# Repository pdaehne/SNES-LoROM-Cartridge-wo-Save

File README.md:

# Super Nintendo LoROM Cartridge without Save

This repository contains the KiCad project and Gerber files for a Super Nintendo
LoROM Cartridge without Save functionality that allows to create replica
cartridges using 27C400, 27C800 and 27C160 EPROMS. When you have SNES
cartridge images (usually SFC files), you can burn one or more of them onto the
EPROM (depending on the size), and use the cartridge on your SNES like a normal
cartridge.

What is a LoROM cartridge, and how do you know that a given cartridge image
needs a LoROM cartridge PCB? Well, there are three types of SNES cartridges,
LoROM, HiROM and ExHiROM. Most cartridge images have a header that specifies
the type of cartridge (a notable exception are the test cartridges, which are
both LoROM cartridges, but do not have a header). There are software tools out
there that allow you to view the information in the cartridge image, and you
can use such a tool to determine whether a given image needs a LoROM, HiROM or
ExHiROM cartridge PCB.

## Ordering the PCB

The subdirectory "gerber-files" contains a Zip file you can use to order the PCB
from PCB manufacturers like PCBWay or JLCPCB. Simply upload the Zip on their web
page.

> [!IMPORTANT]
> SNES cartridges have a thickness of 1.2mm, not the default thickness of 1.6mm!
> Make sure that you order your PCBs with a thickness of 1.2mm. I also recommend
> to order a surface finish of ENIG with gold fingers and chamfered edges,
> because it is much more durable than the default HASL finish.

## Building the Cartridge

### Bill of Materials

* __1x 27C400, 27C800 or 27C160 EPROM__.

  This is where you store your cartridge images. 27C400 have a capacity of
  512 KiB, 27C800 a capacity of 1 MiB, and 27C160 a capacity of 2 MiB.

* (Optional) __1x 42 Pin Socket 2.54mm pitch 15.42mm width__.

  This is the socket for the EPROM. It is optional, you can also solder the
  EPROM directly to the PCB, but I prefer to use sockets. Keep in mind that the
  cartridge will not fit into a cartridge shell when you use sockets.

* __1x PIC12F629-I/P DIP-8__.

  This microcontroller simulates the CIC chip that is required on SNES
  cartridges. When powering on the console, the SNES communicates with this
  chip and starts the cartridge only when it is convinced that there is a
  legit CIC chip on the cartridge. This was a security scheme enforced by
  Nintendo to make sure that only properly licensed cartridges worked on the
  SNES. Today, this scheme is cracked, and we use this PIC instead of a real
  CIC.

* (Optional) __1x 8 Pin Socket 2.54mm pitch 7.62mm width__.

  This is the socket for the PIC12F629. It is optional, you can also solder the
  PIC directly to the PCB.

* __2x 100nF Ceramic Capacitors__.

  These are the decoupling capacitors for the EPROM and the PIC.

* __1x 22&mu;F Electrolytic Capacitor__.

  Another capacitor that improves the power supply for the ICs on the cartridge.

* (Optional) __3x 10kOhm Resistors__.

  Three pull-up resistors, one for the "/PAIR" input of the PIC (required), and
  two for the address lines A18 and A19 which get switched by the DIP switch
  (optional, only required when you actually install the DIP switch).

* (Optional) __1x DIP Switch 2 Pin__.

  This DIP switch is optional, it allows you to put multiple (up to four) images
  onto the cartridge and select one of them by switching the address lines A18
  and A19 of the EPROM. When you plan to put only one image onto the cartridge,
  you do not need this DIP switch and its two corresponding pull-up resistors,
  instead close two corresponding jumpers on the other side of the PCB.

### Soldering the Socket for the EPROM (U1)

Start with soldering the large 42 pin socket for the EPROM (U1). This socket is
optional, you can also solder the EPROM directly to the PCB, but I prefer to use
sockets. Keep in mind that the cartridge will not fit into a cartridge shell
when you use sockets.

When you solder the EPROM directly to the PCB, you have program it before doing
so! See below for more information.

Make sure the little notch of the socket is aligned with the little notch on the
silk screen (to the right in the image below).

### Soldering the Socket for the PIC12F629 (U2)

Now solder the small 8 pin socket for the PIC12F629 (U2). This socket is also
optional, you can also solder the PIC directly to the PCB.

When you solder the PIC directly to the PCB, you have program it before doing
so! See below for more information.

Make sure the little notch of the socket is aligned with the little notch on the
silk screen (to the right in the image below).

### Soldering the Decoupling Capacitors C1 and C2

Solder the two decoupling capacitors C1 and C2 for the EPROM and the PIC.

### Soldering the Pullup Resistors R1, R2 and R3

Solder the three pullup resistors R1, R2 and R3. R1 and R2 are the pullup
resistors for the address lines A18 and A19. They are optional, you only need to
install them when you install the DIP switch (see next step for more
information). R3 is the pullup resistor for the "/PAIR" input of the PIC and is
required.

### Soldering the DIP Switch

The DIP switch is optional, it is only required when you plan to put more than
one cartridge image onto the EPROM. When you install it, you also have to
install the pullup resistors R1 and R2. When you do not install it, you have to
close the corresponding jumpers on the other side of the PCB with a blob of
solder.

### Soldering the Capacitor C3

The last step is to solder the electrolytic capacitor C3. I recommend to bend
the legs of the capacitor so that it lies flat on the PCB. Keep in mind that the
orientation of this capacitors matters. The silk screen shows a small + on the
positive side of the footprint (left in the photo below), and a thick white
stripe on the negative side (right in the photo). The capacitor also has a white
stripe on its enclosure that marks the negative side. Another hint is the length
of the legs - the long leg is the positive side, and the short leg is the
negative side.

## Programming the Firmware on the PIC12F629

On each cartridge there has to be a CIC chip that proves to the console that
this is a legit cartridge licensed by Nintendo. Nowadays, this security chip is
cracked, and we can simulate it with a cheap PIC microprocessor and a special
firmware. The firmware is called "supercic", and precompiled versions
(.hex-Files) are available for download here:

https://sd2snes.de/blog/cool-stuff/supercic

The actual source code (if you are interested) is available on Github:

https://github.com/mrehkopf/sd2snes/tree/master/cic/supercic

What you need for programming the PIC is the file "supercic-key_p12f629.hex"
inside the zip file from the first link and of course a programmer. I own the
popular TL866 II Plus and will demonstrate how to install the firmware using
this programmer and the corresponding Xgpro software, but the approach will be
similar when using other types of programmers.

First, insert the PIC12F629 into the programmer like shown in the picture above.
The notch faces the lever (right in the image).

Then, start the Xgpro software, select the PIC12F629 IC, load
"supercic-key_p12f629.hex", and program the PIC. It is important to realize that
the .hex-File contains three parts, the Flash (code) section with the firmware,
the EEPROM (persistent memory) section with the PAL/NTSC flag, and the Fuses.
The Xgpro software will programm all three sections in one go, but when you use
another programmer and software combination, you might have to program these
three parts separately. Either way, carefully check that all parts got
programmed correctly, otherwise the cartridge will not work.

## Programming Cartridge Images on the EPROM

Now, we will programm the EPROM with the cartridge images. First of all, you
have to think about the layout of your cartridge images on the EPROM. This
depends on the size of your images and the size of your EPROM.

When you use a 27C400 EPROM, you have one single slot of 512 KiB where you can
program one single image with up to 512 KiB.

When you use a 27C800 EPROM, you have two slots of 512 KiB each. You can fill
these slots with two images of up to 512 KiB, one image in slot 1, and another
image in slot 2. Or you can fill these slots with one single image of up to 1
MiB that occupies both slots 1 and 2.

When you use a 27C160 EPROM, you have four slots of 512 KiB each. You can fill
these slots with four images up to 512 KiB, one image in each of the four slots.
Or you can fill these slots with two images of up to 1 MiB, one in slots 1 and
2, and the other in slots 3 and 4. You can also mix two images of 512 KiB with
one image of 1 MiB, with the two 512 KiB images in slots 1 and 2, and the 1 MiB
image in slots 2 and 3, or the other way round (the 1 MiB image in slots 1 and
2, and the two 512 KiB images in slots 3 and 4). Keep in mind that the start of
the 1 MiB image must be aligned to 1 MiB, i.e. putting a 1 MiB image into slots
2 and 3 is not possible! Finally, you can fill the slots with one single image
of up to 2 MiB that occupies slots 1, 2, 3 and 4.

As an example, I will programm a 27C160 EPROM (4 slots) for a test cartridge.
This cartridge will consist of the the following three cartridge images:

1. The "NTF 2.5 Test Cartridge", available here:

   https://tcrf.net/NTF_2.5_Test_Cartridge

   This is a 1 MiB image and will occupy slots 1 and 2.

2. The "Burn-in / Test Cartridge", available here:

   https://tcrf.net/Burn-in_-_Test_Cartridge

   This is a 512 KiB image and will occupy slot 3.

3. The "240p Test Suite", available here:

   https://artemiourbina.itch.io/240p-test-suite

   This is a 512 KiB image and will occupy slot 4.

My TL866 programmer is not able to programm the kinds of EPROMs needed for the
cartridge, but there are adapters available. I'm using the adapter from this
project:

https://github.com/mafe72/27c160-tl866-adapter

There are other alternatives available, for example this project:

https://github.com/keirf/pcb-projects/wiki/EPROM-Adapter-v4

Put the adapter into the TL866, and put the EPROM into the adapter as shown in
the image above.

These adapters are not able to programm the 27C160 in one single pass, instead
you have to write chunks of 512 KiB, which coincides nicely with our slots of
512 KiB. You have to set switches on the adapter to program the chunks into the
right location on the EPROM, but this depends on the adapter you are using. Have
a look into the manual for your adapter. The whole procedure is quite tedious,
and you have to be fully concentrated not to make an error. The slightest error,
and you have to clear your EPROM in your UV eraser and start over from the
beginning!

In the Xgpro software, select the "AT27C4096 @DIP40" IC. Yes, this is not the
EPROM we are using, but this is the way these adapters work. The 27C4096 is a
512 KiB EPROM that uses the same programming algorithm than our 27C160, and we
use it to program our 27C160 with chunks of 512 KiB. We have to deselect "Check
ID" for obvious reasons as well as "Pin Detect", and we have to set "Puls Delay"
to "50us". Finally, we have to adjust "VPP Voltage", have a look into the
datasheet for your EPROM. The datasheet for my ST M27C160 says that the
programming voltage has be "12.00V".

Now load the cartridge image for the first slot, in our case the "NTF 2.5 Test
Cartridge". This image is 1 MiB, i.e. it is too large, but this is not a
problem, Xgpro will automatically remove the surplus 512 KiB. Configure your
adapter for writing the first slot, and program the image.

Now we have to program the second half of the "NTF 2.5 Test Cartridge" into the
second slot. Again load the cartridge image, but in the file load dialog, set
the "From File Start Addr(Hex)" to "40000" (this is 512 KiB in [hexadecimal
notation](https://en.wikipedia.org/wiki/Hexadecimal)). Leave all the other
settings as for the first slot, configure your adapter for the second slot, and
program the second half of the image.

Now we have to program the "Burn-in / Test Cartridge" into the third slot. Load
the image, and make sure that in the file load dialog the "From File Start
Addr(Hex)" is set back to "00000". Leave all the other settings as for the first
two slots, configure your adapter for the third slot, and program the image.

Finally, we have to program the "240p Test Suite" into the fourth slot. You know
the drill. Load the image, leave all the other settings as before, configure
your adapter for the fourth slot, and program the image. Finished!

## Using the Cartridge and Troubleshooting

When you do not install your cartridge into a cartridge shell, you have to be
extremly careful when inserting the cartridge. Especially, you have to mind the
orientation: It is a little bit counter intuitive, but you have to insert the
cartridge backwards, with the components on the cartridge facing the back side
of the console! Also keep in mind that the cartridge slot in the console is much
wider than the edge connector of the cartridge because it has extension pins on
both sides that the cartridge does not use, so make sure to insert your
cartridge properly into the center section of the cartridge slot. And when you
remove the cartridge, do not use the eject button, and be careful that the
cartridge does not get stuck in the cover that protects the cartridge slot!

When you have more than one cartridge image programmed on your EPROM, you can
use the dip switches on the cartridge to select the image to start. To start
a given image on the EPROM, you have the select the slot where the image starts
with the two DIP switches:

* To select the image that starts at slot 1, switch both A18 and A19 to "on".

* To select the image that starts at slot 2, switch A18 to "off" and and A19 to
  "on".

* To select the image that starts at slot 3, switch A18 to "on" and and A19 to
  "off".

* To select the image that starts at slot 4, switch both A18 and A19 to "off".

| Slot 1                           | Slot 2                           | Slot3                            | Slot4                            |
|----------------------------------|----------------------------------|----------------------------------|----------------------------------|
|||||

As an example, lets have a look at the example cartridge we programmed in the
previous section. First, we want to start the "NTF 2.5 Test Cartridge". This
image starts in slot 1. So we have to move both DIP switches for A18 and A19 to
the "on" position.

Now we want to start the "Burn-in / Test Cartridge". This image starts in slot
3. So we have to move the DIP switch for address line A18 to "on", and the
DIP switch for address line A19 to "off".

Finally we want to start the "240p Test Suite". This image starts in slot 4. So
we have to move both DIP switches for A18 and A19 to the "off" position.

What happens when we select slot 2 on this cartridge, i.e. when we switch A18 to
"off" and A19 to "on"? Well, we will probably just get a black screen, because
we try to start a cartridge image in the middle of the "NTF 2.5 Test Cartridge",
and the console immediately crashes.

When the cartridge does not work, there are two different failure modes:

1. You do not get a video signal at all. This means that the PIC12F629 on the
   cartridge was not able to unlock the SNES. When you have a PAL (european)
   SNES and try to use the cartridge for the first time, this is actually
   normal, because the firmware on the PIC simulates a NTSC (american) lockout
   chip. Simply press Reset or powercycle the console, it should automatically
   switch to PAL when the unlock sequence fails. When this does not help, check
   if the firmware is burned correctly to your PIC and that the orientation of
   the PIC on the cartridge is correct (the notch on the chip should face to
   the center of the cartridge). Also check your soldering.

2. You get a video signal, but the screen is all black or completly garbled.
   This means that the SNES is not able to correctly read the contents of the
   EPROM. Usually that can be fixed by wiggling the cartridge carefully a little
   bit in the slot. When that does not work, remove the cartridge an try to
   clean the edge connector, especially remove any flux that might be left over
   from soldering the cartridge. When this also does not help, you have to check
   that the EPROM is correctly programmed, that it has the right orientation
   (the notch should face the DIP switches), and that you set the DIP switches
   correctly. Also check your soldering.

## License

SNES LoROM Cartridge w/o Save (c) by Patrick Dähne

SNES LoROM Cartridge w/o Save is licensed under a
Creative Commons Attribution-NonCommercial-ShareAlike 4.0 International License.

You should have received a copy of the license along with this
work. If not, see <https://creativecommons.org/licenses/by-nc-sa/4.0/>.

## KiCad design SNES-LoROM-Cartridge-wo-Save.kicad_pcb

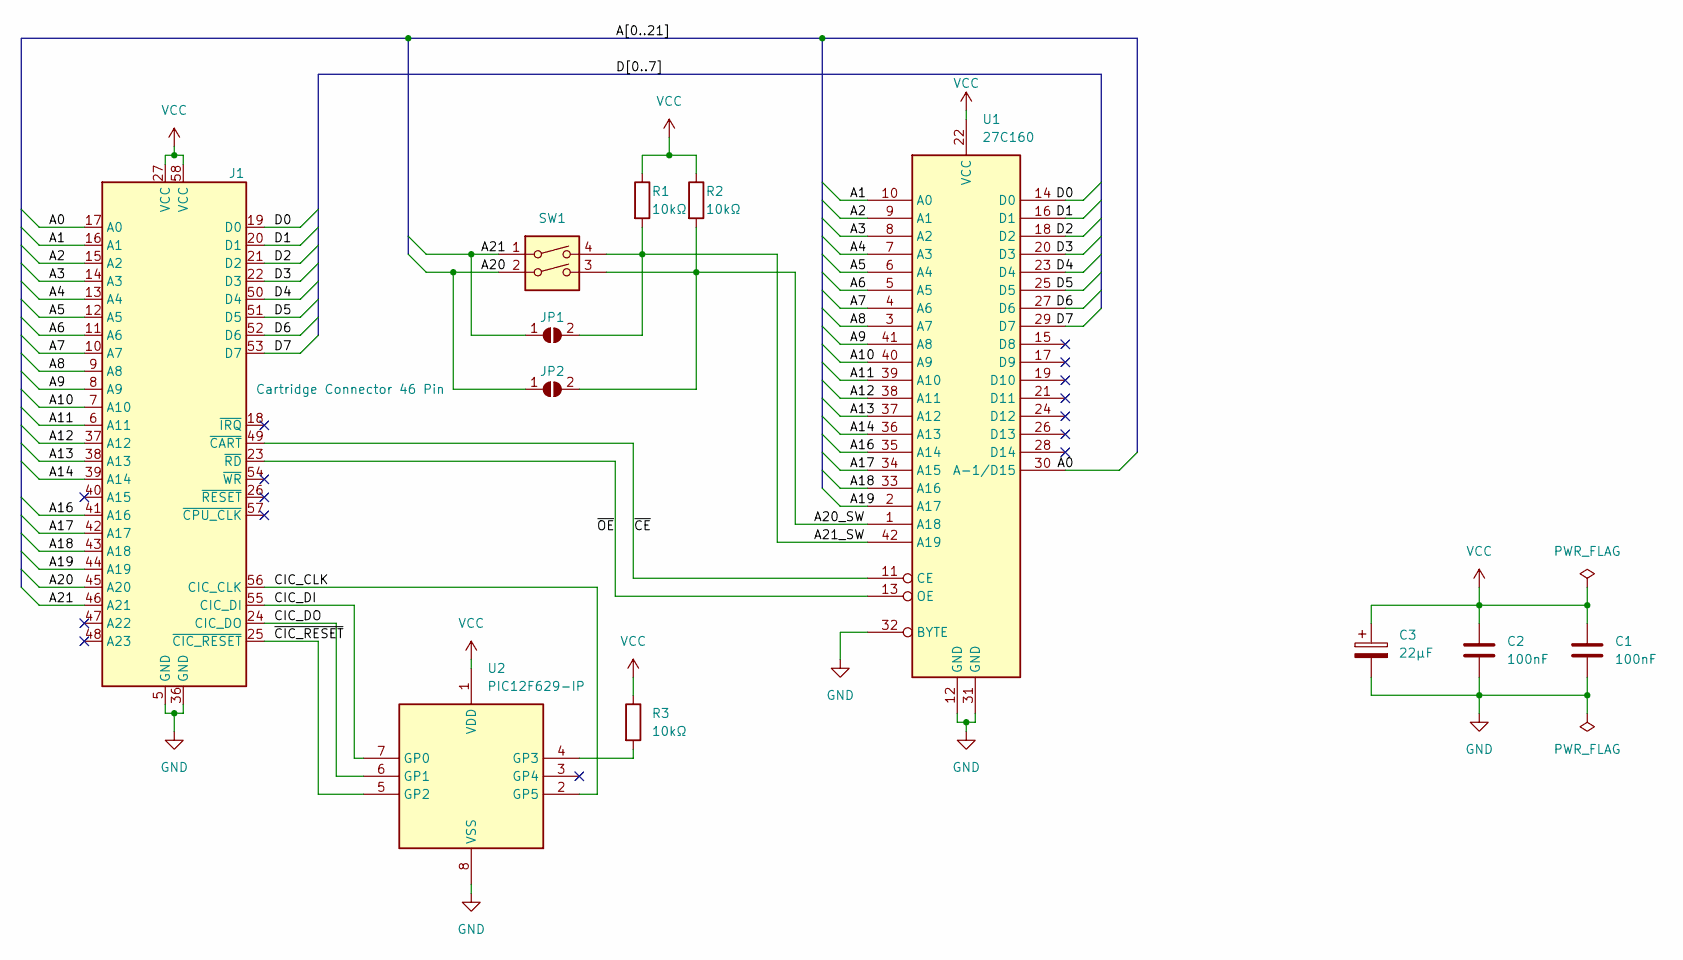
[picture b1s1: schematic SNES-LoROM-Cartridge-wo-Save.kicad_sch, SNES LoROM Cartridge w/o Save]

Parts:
C1, C2: 100nF; C_Rect_L4.6mm_W2.0mm_P2.50mm_MKS02_FKP02
C3: 22µF; CP_Radial_D5.0mm_P2.00mm
J1: Cartridge Connector 46 Pin; SNES Cartridge Connector 46 Pins
JP1, JP2: SolderJumper_2_Open; SolderJumper-2_P1.3mm_Open_RoundedPad1.0x1.5mm
R1, R2, R3: 10kΩ; R_Axial_DIN0207_L6.3mm_D2.5mm_P10.16mm_Horizontal
SW1: SW_DIP_x02; SW_DIP_SPSTx02_Slide_9.78x7.26mm_W7.62mm_P2.54mm
U1: 27C160; DIP-42_W15.24mm_LongPads
U2: PIC12F629-IP; DIP-8_W7.62mm

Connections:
/A0: J1.17 (A0), U1.30 (A-1/D15)
/A1: J1.16 (A1), U1.10 (A0)
/A2: J1.15 (A2), U1.9 (A1)
/A3: J1.14 (A3), U1.8 (A2)
/A4: J1.13 (A4), U1.7 (A3)
/A5: J1.12 (A5), U1.6 (A4)
/A6: J1.11 (A6), U1.5 (A5)
/A7: J1.10 (A7), U1.4 (A6)
/A8: J1.9 (A8), U1.3 (A7)
/A9: J1.8 (A9), U1.41 (A8)
/A10: J1.7 (A10), U1.40 (A9)
/A11: J1.6 (A11), U1.39 (A10)
/A12: J1.37 (A12), U1.38 (A11)
/A13: J1.38 (A13), U1.37 (A12)
/A14: J1.39 (A14), U1.36 (A13)
/A16: J1.41 (A16), U1.35 (A14)
/A17: J1.42 (A17), U1.34 (A15)
/A18: J1.43 (A18), U1.33 (A16)
/A19: J1.44 (A19), U1.2 (A17)
/A20: J1.45 (A20), JP2.1 (A), SW1.2
/A20_SW: JP2.2 (B), R2.2, SW1.3, U1.1 (A18)
/A21: J1.46 (A21), JP1.1 (A), SW1.1
/A21_SW: JP1.2 (B), R1.2, SW1.4, U1.42 (A19)
/CIC_CLK: J1.56 (CIC_CLK), U2.2 (GP5)
/CIC_DI: J1.55 (CIC_DI), U2.7 (GP0)
/CIC_DO: J1.24 (CIC_DO), U2.6 (GP1)
/D0: J1.19 (D0), U1.14 (D0)
/D1: J1.20 (D1), U1.16 (D1)
/D2: J1.21 (D2), U1.18 (D2)
/D3: J1.22 (D3), U1.20 (D3)
/D4: J1.50 (D4), U1.23 (D4)
/D5: J1.51 (D5), U1.25 (D5)
/D6: J1.52 (D6), U1.27 (D6)
/D7: J1.53 (D7), U1.29 (D7)
/~CE: J1.49 (~CART), U1.11 (CE)
/~CIC_RESET: J1.25 (~CIC_RESET), U2.5 (GP2)
/~OE: J1.23 (~RD), U1.13 (OE)
GND: C1.2, C2.2, C3.2, J1.5 (GND), J1.36 (GND), U1.12 (GND), U1.31 (GND), U1.32 (BYTE), U2.8 (VSS)
unnamed: R3.2, U2.4 (GP3)
VCC: C1.1, C2.1, C3.1, J1.27 (VCC), J1.58 (VCC), R1.1, R2.1, R3.1, U1.22 (VCC), U2.1 (VDD)

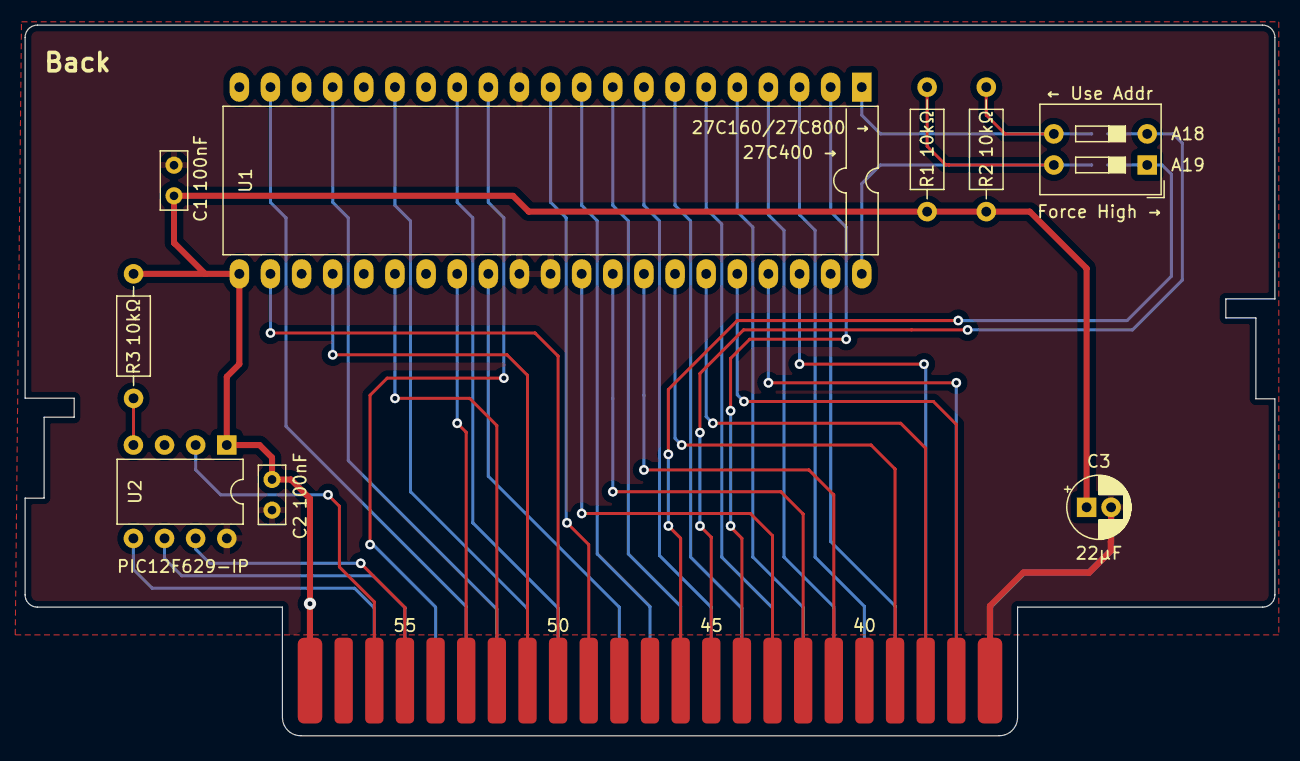
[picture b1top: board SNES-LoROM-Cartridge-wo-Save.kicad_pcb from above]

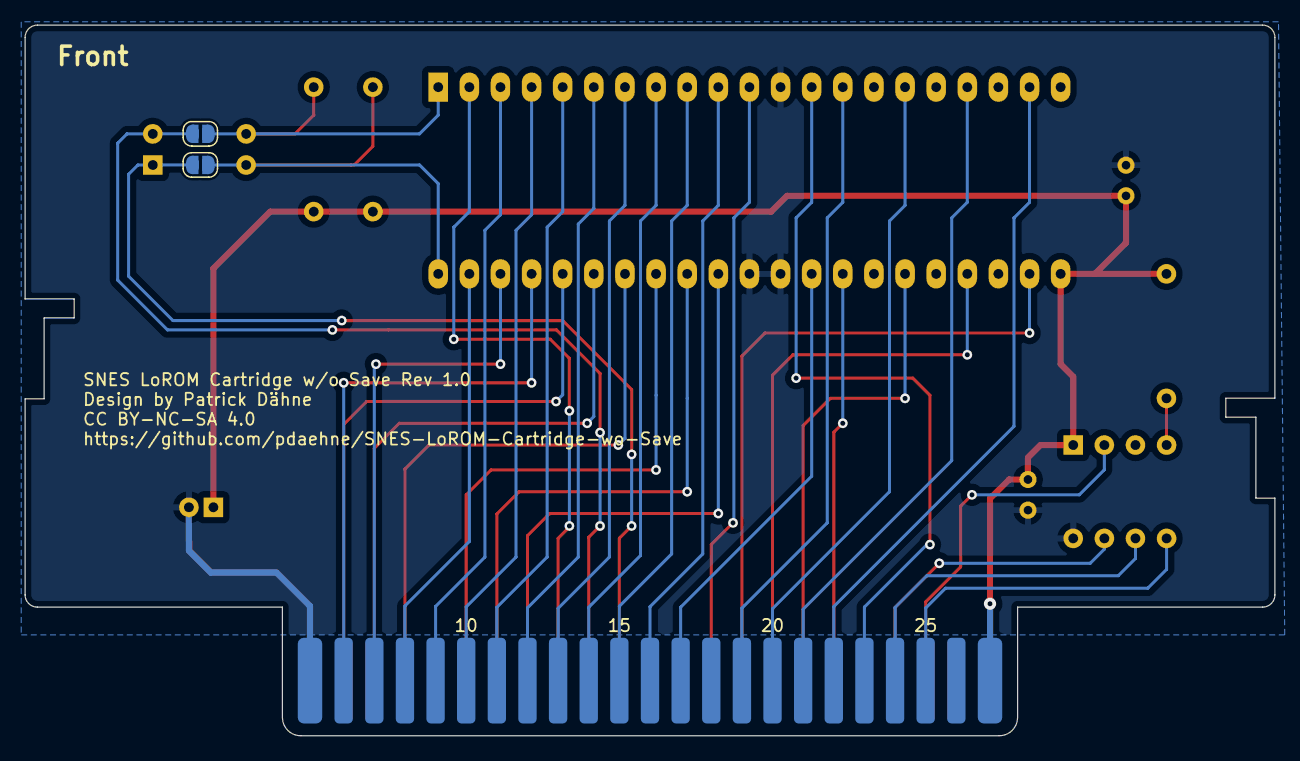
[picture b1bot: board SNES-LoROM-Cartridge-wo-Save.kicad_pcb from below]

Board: 2 copper layers, 102.0 x 58.0 mm, 12 parts (2 on the bottom side), 40 nets.

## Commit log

2024-10-09 Initial check-in
2024-10-10 Removed gitignore rule which clashes with the project name
2024-10-10 Added missing PCB file
2024-10-10 Fixed copy and paste error
2024-10-10 Remove alpha channel
2025-01-20 Fixed access rights
2025-12-02 Fixed typos
2025-12-02 Fixed URL

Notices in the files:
README.md:
SNES LoROM Cartridge w/o Save (c) by Patrick Dähne
SNES LoROM Cartridge w/o Save is licensed under a
Creative Commons Attribution-NonCommercial-ShareAlike 4.0 International License.
You should have received a copy of the license along with this
work. If not, see .
SNES-LoROM-Cartridge-wo-Save.kicad_pcb:
Patrick Dähne CC BY-NC-SA 4.0
CC BY-NC-SA 4.0
